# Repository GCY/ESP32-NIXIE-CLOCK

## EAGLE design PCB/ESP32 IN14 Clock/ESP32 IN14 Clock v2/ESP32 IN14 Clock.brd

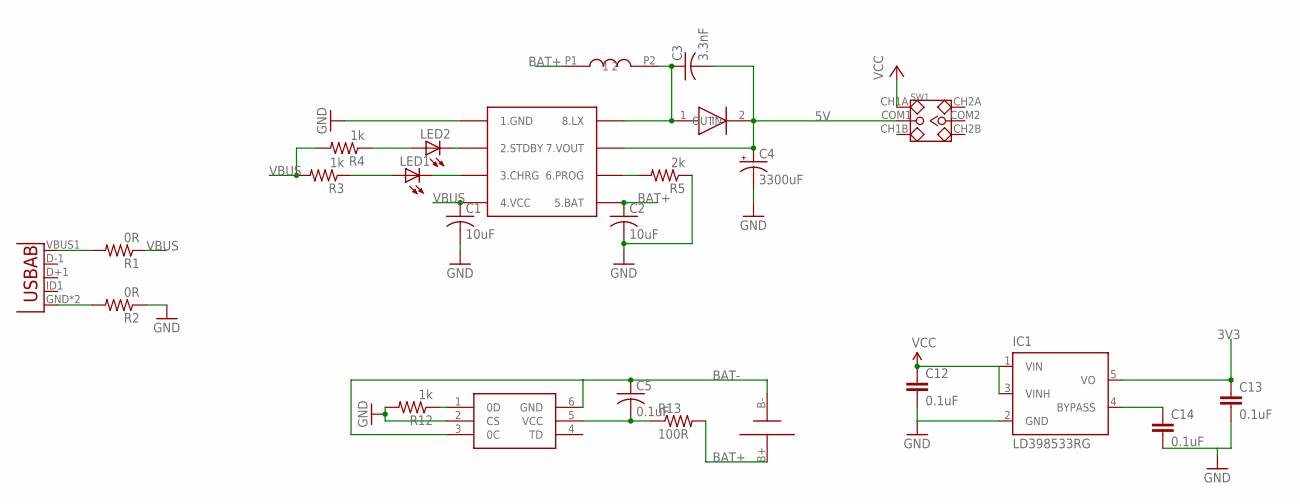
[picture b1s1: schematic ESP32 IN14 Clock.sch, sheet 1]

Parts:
C1, C2: 10uF; C1206
C3: 3.3nF; C1206
C4: 3300uF; E7,5-18
C5: 0.1uF; C1206
C12, C13, C14: 0.1uF; 1206
IC1: LD398533RG; TSOT23-5L
L2: 3.3uH; CD54
LED1, LED2: LEDCHIPLED_0805; CHIPLED_0805
R1, R2: 0R; M0805
R3, R4, R12: 1k; M0805
R5: 2k; M0805
R13: 100R; M0805
SW1: SMD-TOGGLE-SWITCH-2CH(2X3P-7X3.5MM); SW6-2.54-SMD-7.0X3.5X1.5MM
U1: USB""; USB-MICRO-SMD
U2: FM6316FE; SOP-8
U3: DW06; SOT23-6
U$1: SMA-SS34
U$2: 18650SMD

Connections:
3V3: C13.1, IC1.5 (VO); also elsewhere on the board
5V: C3.2, C4.+, SW1.COM1, U2.7 (7.VOUT), U$1.2 (OUT)
BAT+: C2.1, L2.P1 (1), R13.2, U2.5 (5.BAT), U$2.B+
BAT-: C5.1, U3.3 (0C), U3.6 (GND), U$2.B-
GND: C1.2, C2.2, C4.-, C12.2, C13.2, C14.2, IC1.2 (GND), R2.1, R5.1, R12.2, U2.1 (1.GND), U3.2 (CS); also elsewhere on the board
unnamed: R1.2, U1.VBUS1 (VBUS)
unnamed: R2.2, U1.GND, U1.GND1 (GND)
unnamed: LED1.C, U2.3 (3.CHRG)
unnamed: LED1.A, R3.1
unnamed: LED2.C, U2.2 (2.STDBY)
unnamed: R5.2, U2.6 (6.PROG)
unnamed: C3.1, L2.P2 (2), U2.8 (8.LX), U$1.1 (IN)
unnamed: R12.1, U3.1 (0D)
unnamed: C5.2, R13.1, U3.5 (VCC)
unnamed: C14.1, IC1.4 (BYPASS)
unnamed: LED2.A, R4.1
VBUS: C1.1, R1.1, R3.2, R4.2, U2.4 (4.VCC)
VCC: C12.1, IC1.1 (VIN), IC1.3 (VINH), SW1.CH1A; also elsewhere on the board

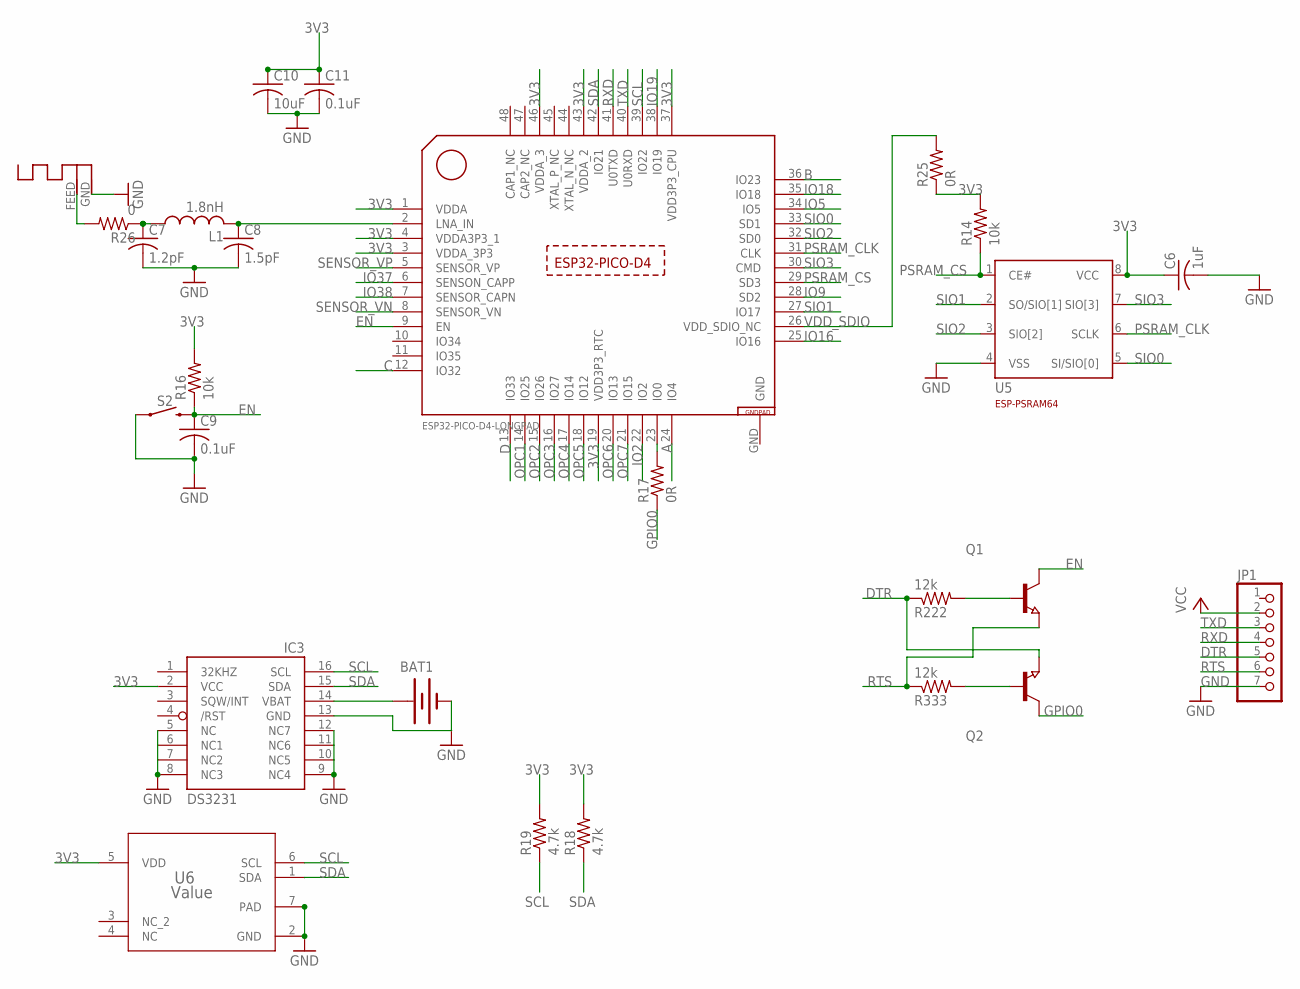
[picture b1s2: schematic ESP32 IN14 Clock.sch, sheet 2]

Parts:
ANT1: ANTENNA; RN-ANT
BAT1: BATTERY20PTH; BATTCOM_20MM_PTH
C6: 1uF; C1206
C7: 1.2pF; C1206
C8: 1.5pF; C1206
C9, C11: 0.1uF; C1206
C10: 10uF; C1206
IC3: DS3231/SO; SO16W
JP1: PINHD-1X7; 1X07
L1: 1.8nH; RESC0805_L
Q1, Q2: NPN-TRANSISTOR_SOT23W; SOT23W
R14, R16: 10k; 0603-RES
R17, R25: 0R; 0603-RES
R18, R19: 4.7k; 0603-RES
R26: 0; 0603-RES
R222, R333: 12k; M0805
S2: MOMENTARY-SWITCH-SPST-SMD-6.0X3.5MM; TACTILE_SWITCH_SMD_6.0X3.5MM
U4: ESP32-PICO-D4-LONGPAD; QFN48
U5: ESP-PSRAM64; SOT23-8
U6: Value; DMB0006A

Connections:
3V3: C6.1, C10.1, C11.1, IC3.2 (VCC), R14.2, R16.2, R18.2, R19.2, R25.1, U4.1 (VDDA), U4.3 (VDDA_3P3), U4.4 (VDDA3P3_1), U4.19 (VDD3P3_RTC), U4.37 (VDD3P3_CPU), U4.43 (VDDA_2), U4.46 (VDDA_3), U5.8 (VCC), U6.5 (VDD); also elsewhere on the board
A: U4.24 (IO4); also elsewhere on the board
B: U4.36 (IO23); also elsewhere on the board
C: U4.12 (IO32); also elsewhere on the board
D: U4.13 (IO33); also elsewhere on the board
DTR: JP1.5, Q2.3 (E), R222.1
EN: C9.1, Q1.2 (C), R16.1, S2.2, U4.9 (EN)
GND: ANT1.GND, BAT1.2 (-), C6.2, C7.2, C8.2, C9.2, C10.2, C11.2, IC3.5 (NC), IC3.6 (NC1), IC3.7 (NC2), IC3.8 (NC3), IC3.9 (NC4), IC3.10 (NC5), IC3.11 (NC6), IC3.12 (NC7), IC3.13 (GND), JP1.7, S2.1, U4.GND, U5.4 (VSS), U6.2 (GND), U6.7 (PAD); also elsewhere on the board
GPIO0: Q2.2 (C), R17.1
IO2: U4.22 (IO2)
IO5: U4.34 (IO5)
IO9: U4.28 (SD2)
IO16: U4.25 (IO16)
IO18: U4.35 (IO18)
IO19: U4.38 (IO19)
IO37: U4.6 (SENSON_CAPP)
IO38: U4.7 (SENSOR_CAPN)
unnamed: ANT1.FEED, R26.2
unnamed: R17.2, U4.23 (IO0)
unnamed: Q1.1 (B), R222.2
unnamed: Q2.1 (B), R333.2
unnamed: C8.1, L1.2, U4.2 (LNA_IN)
unnamed: C7.1, L1.1, R26.1
unnamed: BAT1.1 (+), IC3.14 (VBAT)
OPC1: U4.14 (IO25); also elsewhere on the board
OPC2: U4.15 (IO26); also elsewhere on the board
OPC3: U4.16 (IO27); also elsewhere on the board
OPC4: U4.17 (IO14); also elsewhere on the board
OPC5: U4.18 (IO12); also elsewhere on the board
OPC6: U4.20 (IO13); also elsewhere on the board
OPC7: U4.21 (IO15); also elsewhere on the board
PSRAM_CLK: U4.31 (CLK), U5.6 (SCLK)
PSRAM_CS: R14.1, U4.29 (SD3), U5.1 (CE#)
RTS: JP1.6, Q1.3 (E), R333.1
RXD: JP1.4, U4.41 (U0TXD)
SCL: IC3.16 (SCL), R19.1, U4.39 (IO22), U6.6 (SCL)
SDA: IC3.15 (SDA), R18.1, U4.42 (IO21), U6.1 (SDA)
SENSOR_VN: U4.8 (SENSOR_VN)
SENSOR_VP: U4.5 (SENSOR_VP)
SIO0: U4.33 (SD1), U5.5 (SI/SIO[0])
SIO1: U4.27 (IO17), U5.2 (SO/SIO[1])
SIO2: U4.32 (SD0), U5.3 (SIO[2])
SIO3: U4.30 (CMD), U5.7 (SIO[3])
TXD: JP1.3, U4.40 (U0RXD)
VCC: JP1.2; also elsewhere on the board
VDD_SDIO: R25.2, U4.26 (VDD_SDIO_NC)

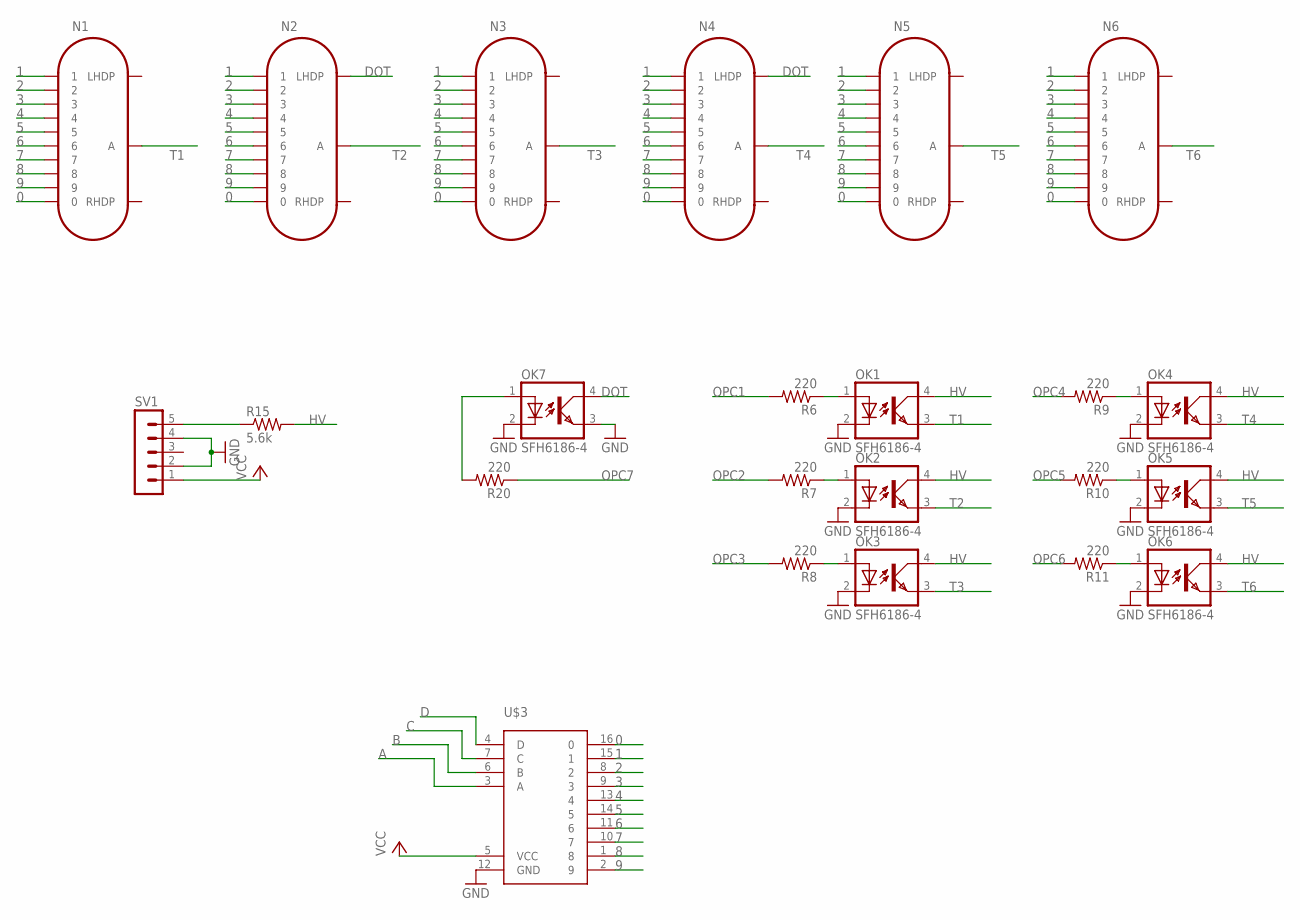
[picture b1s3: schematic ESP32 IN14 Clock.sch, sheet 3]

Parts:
N1, N2, N3, N4, N5, N6: IN-14
OK1, OK2, OK3, OK4, OK5, OK6, OK7: SFH6186-4; SMD4-7
R6, R7, R8, R9, R10, R11, R20: 220; 0603-RES
R15: 5.6k; 0207/12
SV1: MA05-1
U$3: K155ID1; DIL16-KIT

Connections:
0: N1.0, N2.0, N3.0, N4.0, N5.0, N6.0, U$3.16 (0)
1: N1.1, N2.1, N3.1, N4.1, N5.1, N6.1, U$3.15 (1)
2: N1.2, N2.2, N3.2, N4.2, N5.2, N6.2, U$3.8 (2)
3: N1.3, N2.3, N3.3, N4.3, N5.3, N6.3, U$3.9 (3)
4: N1.4, N2.4, N3.4, N4.4, N5.4, N6.4, U$3.13 (4)
5: N1.5, N2.5, N3.5, N4.5, N5.5, N6.5, U$3.14 (5)
6: N1.6, N2.6, N3.6, N4.6, N5.6, N6.6, U$3.11 (6)
7: N1.7, N2.7, N3.7, N4.7, N5.7, N6.7, U$3.10 (7)
8: N1.8, N2.8, N3.8, N4.8, N5.8, N6.8, U$3.1 (8)
9: N1.9, N2.9, N3.9, N4.9, N5.9, N6.9, U$3.2 (9)
A: U$3.3 (A); also elsewhere on the board
B: U$3.6 (B); also elsewhere on the board
C: U$3.7 (C); also elsewhere on the board
D: U$3.4 (D); also elsewhere on the board
DOT: N2.LHDP, N4.LHDP, OK7.4 (COL)
GND: OK1.2 (C), OK2.2 (C), OK3.2 (C), OK4.2 (C), OK5.2 (C), OK6.2 (C), OK7.2 (C), OK7.3 (EMIT), SV1.2, SV1.4, U$3.12 (GND); also elsewhere on the board
HV: OK1.4 (COL), OK2.4 (COL), OK3.4 (COL), OK4.4 (COL), OK5.4 (COL), OK6.4 (COL), R15.2
unnamed: R15.1, SV1.5
unnamed: OK1.1 (A), R6.1
unnamed: OK2.1 (A), R7.1
unnamed: OK3.1 (A), R8.1
unnamed: OK4.1 (A), R9.1
unnamed: OK5.1 (A), R10.1
unnamed: OK6.1 (A), R11.1
unnamed: OK7.1 (A), R20.2
OPC1: R6.2; also elsewhere on the board
OPC2: R7.2; also elsewhere on the board
OPC3: R8.2; also elsewhere on the board
OPC4: R9.2; also elsewhere on the board
OPC5: R10.2; also elsewhere on the board
OPC6: R11.2; also elsewhere on the board
OPC7: R20.1; also elsewhere on the board
T1: N1.A, OK1.3 (EMIT)
T2: N2.A, OK2.3 (EMIT)
T3: N3.A, OK3.3 (EMIT)
T4: N4.A, OK4.3 (EMIT)
T5: N5.A, OK5.3 (EMIT)
T6: N6.A, OK6.3 (EMIT)
VCC: SV1.1, U$3.5 (VCC); also elsewhere on the board

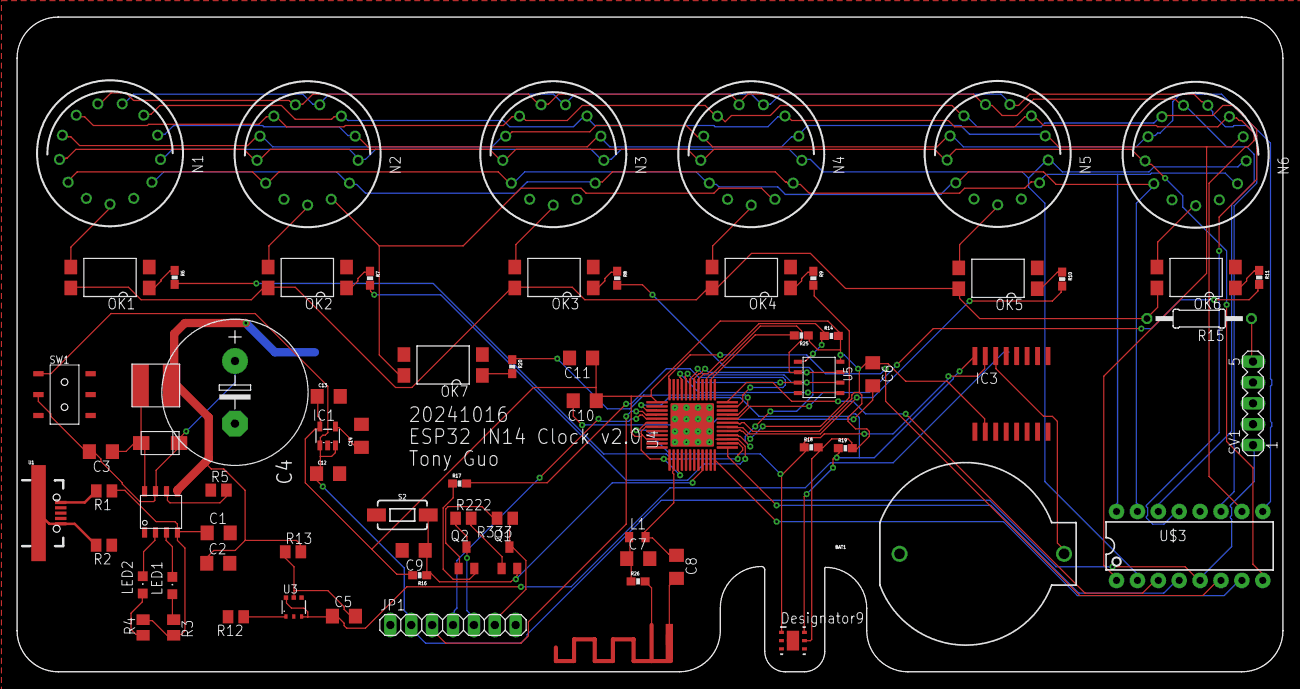
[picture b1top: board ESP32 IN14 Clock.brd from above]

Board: 2 copper layers, 153.9 x 79.6 mm, 74 parts (1 on the bottom side), 77 nets.

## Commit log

2024-12-27 add firmware
2024-12-28 add PCB

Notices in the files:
parts and their libraries:
SparkFun-Capacitors: Licensing: CC v3.0 Share-Alike You are welcome to use this library for commercial purposes.
SparkFun-Switches: Licensing: Creative Commons ShareAlike 4.0 International - https://creativecommons.org/licenses/by-sa/4.0
